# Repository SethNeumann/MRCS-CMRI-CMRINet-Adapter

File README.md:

# REPO NAME: MRCS-CMRI-CMRINet-Adapter

## License: Creative Commons Attribution-NonCommercial-ShareAlike

This is another wiring adapter for classic CMRI boards.  This one is for the CMRINet (RS485) line.  It plugs onto the 5 pin
male molex header (0.156) and brings out 2 sets of 0.100" (2.54mm) or 3.5mm pads for connection to the CMRINet.  This allows
connection without terminating a molex cable.  Note the spacing too tight for two on an SMINI so I've included two sets of screw 
terminals to support the daisy chain.

User Ed Klein requested this adapter.

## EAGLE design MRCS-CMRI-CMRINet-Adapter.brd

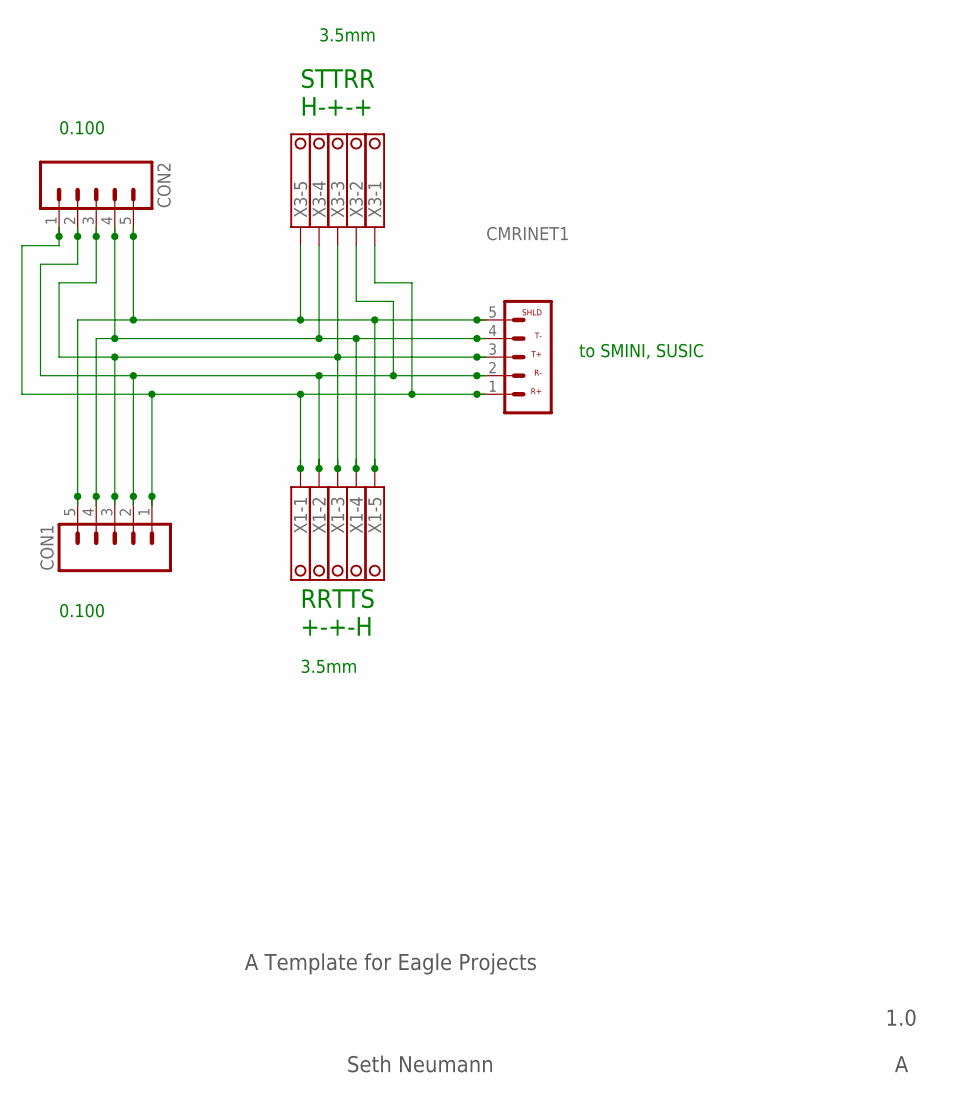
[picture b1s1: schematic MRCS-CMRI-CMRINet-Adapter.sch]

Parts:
CMRINET1: CONNECTOR-CMRINET.156; KK-156-5
CON1, CON2: CONNECTOR-M05LOCK; 1X05_LOCK
X1, X3: 1751277

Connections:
R+: CMRINET1.1, CON1.1, CON2.1, X1.1, X3.1
R-: CMRINET1.2, CON1.2, CON2.2, X1.2, X3.2
SHLD: CMRINET1.5, CON1.5, CON2.5, X1.5, X3.5
T+: CMRINET1.3, CON1.3, CON2.3, X1.3, X3.3
T-: CMRINET1.4, CON1.4, CON2.4, X1.4, X3.4

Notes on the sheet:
A Template for Eagle Projects
1.0
Seth Neumann
to SMINI, SUSIC
0.100
3.5mm
RRTTS +-+-H
STTRR H-+-+

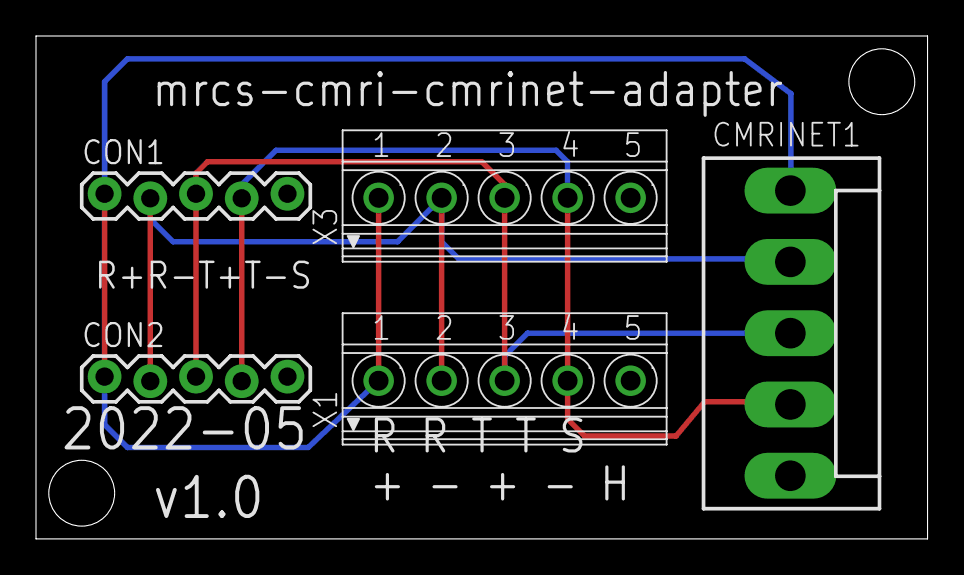
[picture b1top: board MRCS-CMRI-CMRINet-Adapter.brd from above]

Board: 2 copper layers, 49.5 x 27.9 mm, 7 parts (0 on the bottom side), 5 nets.

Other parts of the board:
U$1: CA-PROP65WARNING
U$2: MRCSLOGOBTM

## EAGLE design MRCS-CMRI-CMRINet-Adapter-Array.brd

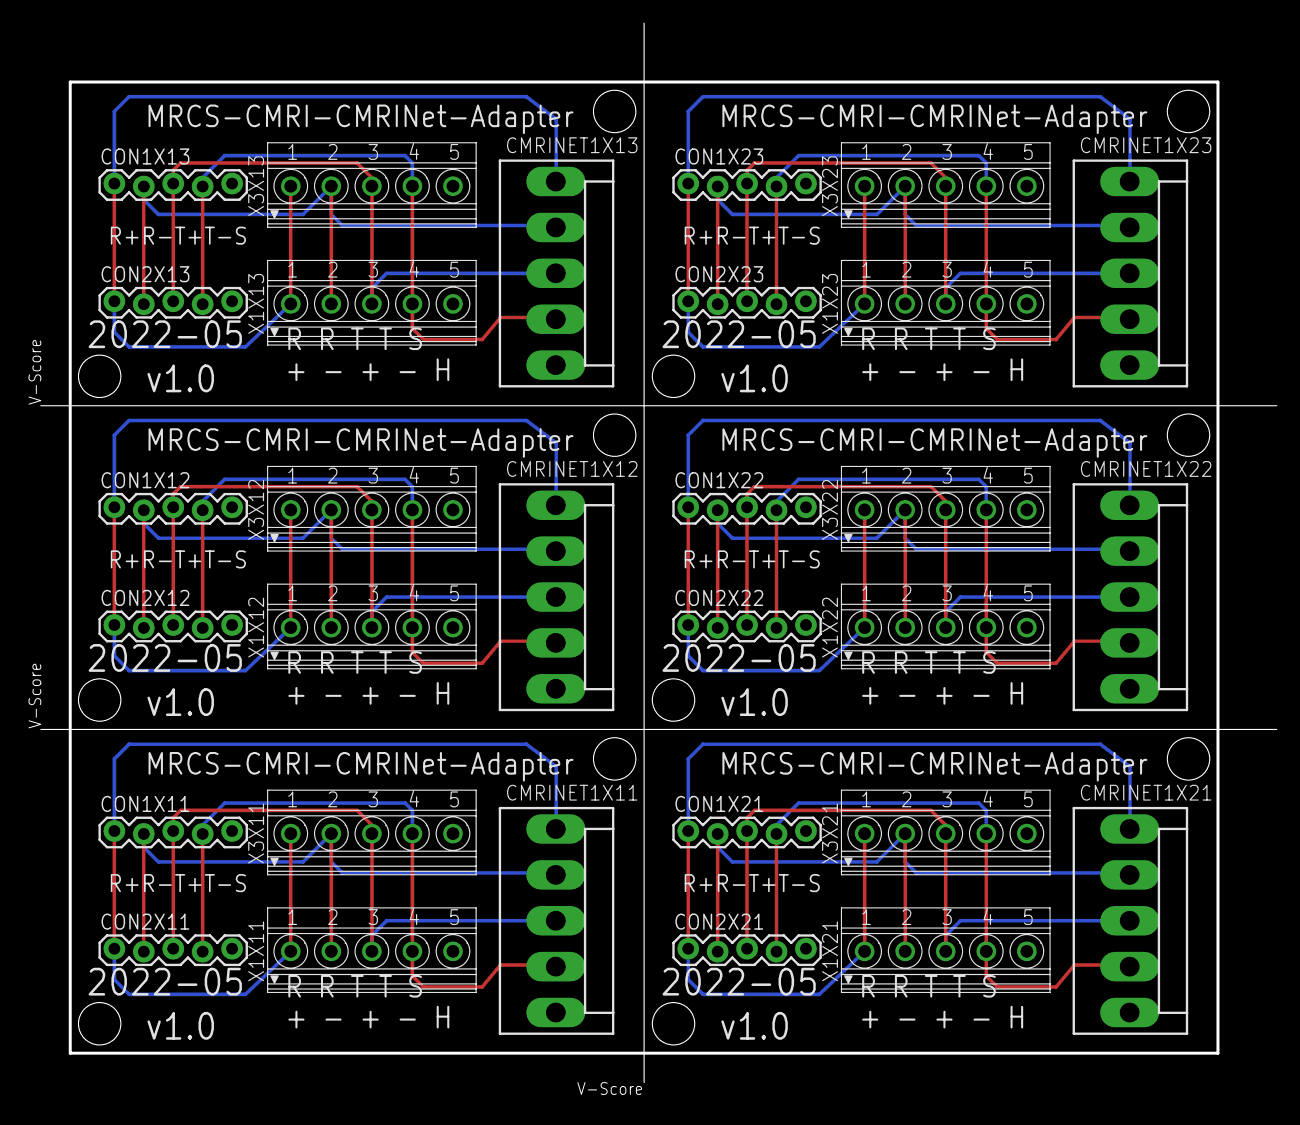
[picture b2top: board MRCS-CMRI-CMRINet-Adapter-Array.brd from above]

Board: 2 copper layers, 107.9 x 92.8 mm, 42 parts (0 on the bottom side), 30 nets.

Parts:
CMRINET1X11, CMRINET1X12, CMRINET1X13, CMRINET1X21, CMRINET1X22, CMRINET1X23: KK-156-5
CON1X11, CON1X12, CON1X13, CON1X21, CON1X22, CON1X23, CON2X11, CON2X12, CON2X13, CON2X21, CON2X22, CON2X23: 1X05_LOCK
U$1X11, U$1X12, U$1X13, U$1X21, U$1X22, U$1X23: CA-PROP65WARNING
U$2X11, U$2X12, U$2X13, U$2X21, U$2X22, U$2X23: MRCSLOGOBTM
X1X11, X1X12, X1X13, X1X21, X1X22, X1X23, X3X11, X3X12, X3X13, X3X21, X3X22, X3X23: 1751277

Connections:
R+X11: CMRINET1X11.1, CON1X11.1, CON2X11.1, X1X11.1, X3X11.1
R+X12: CMRINET1X12.1, CON1X12.1, CON2X12.1, X1X12.1, X3X12.1
R+X13: CMRINET1X13.1, CON1X13.1, CON2X13.1, X1X13.1, X3X13.1
R+X21: CMRINET1X21.1, CON1X21.1, CON2X21.1, X1X21.1, X3X21.1
R+X22: CMRINET1X22.1, CON1X22.1, CON2X22.1, X1X22.1, X3X22.1
R+X23: CMRINET1X23.1, CON1X23.1, CON2X23.1, X1X23.1, X3X23.1
R-X11: CMRINET1X11.2, CON1X11.2, CON2X11.2, X1X11.2, X3X11.2
R-X12: CMRINET1X12.2, CON1X12.2, CON2X12.2, X1X12.2, X3X12.2
R-X13: CMRINET1X13.2, CON1X13.2, CON2X13.2, X1X13.2, X3X13.2
R-X21: CMRINET1X21.2, CON1X21.2, CON2X21.2, X1X21.2, X3X21.2
R-X22: CMRINET1X22.2, CON1X22.2, CON2X22.2, X1X22.2, X3X22.2
R-X23: CMRINET1X23.2, CON1X23.2, CON2X23.2, X1X23.2, X3X23.2
SHLDX11: CMRINET1X11.5, CON1X11.5, CON2X11.5, X1X11.5, X3X11.5
SHLDX12: CMRINET1X12.5, CON1X12.5, CON2X12.5, X1X12.5, X3X12.5
SHLDX13: CMRINET1X13.5, CON1X13.5, CON2X13.5, X1X13.5, X3X13.5
SHLDX21: CMRINET1X21.5, CON1X21.5, CON2X21.5, X1X21.5, X3X21.5
SHLDX22: CMRINET1X22.5, CON1X22.5, CON2X22.5, X1X22.5, X3X22.5
SHLDX23: CMRINET1X23.5, CON1X23.5, CON2X23.5, X1X23.5, X3X23.5
T+X11: CMRINET1X11.3, CON1X11.3, CON2X11.3, X1X11.3, X3X11.3
T+X12: CMRINET1X12.3, CON1X12.3, CON2X12.3, X1X12.3, X3X12.3
T+X13: CMRINET1X13.3, CON1X13.3, CON2X13.3, X1X13.3, X3X13.3
T+X21: CMRINET1X21.3, CON1X21.3, CON2X21.3, X1X21.3, X3X21.3
T+X22: CMRINET1X22.3, CON1X22.3, CON2X22.3, X1X22.3, X3X22.3
T+X23: CMRINET1X23.3, CON1X23.3, CON2X23.3, X1X23.3, X3X23.3
T-X11: CMRINET1X11.4, CON1X11.4, CON2X11.4, X1X11.4, X3X11.4
T-X12: CMRINET1X12.4, CON1X12.4, CON2X12.4, X1X12.4, X3X12.4
T-X13: CMRINET1X13.4, CON1X13.4, CON2X13.4, X1X13.4, X3X13.4
T-X21: CMRINET1X21.4, CON1X21.4, CON2X21.4, X1X21.4, X3X21.4
T-X22: CMRINET1X22.4, CON1X22.4, CON2X22.4, X1X22.4, X3X22.4
T-X23: CMRINET1X23.4, CON1X23.4, CON2X23.4, X1X23.4, X3X23.4

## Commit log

2022-05-08 final tweaks on first pass of adapter
    Changed the 5 position 3.5mm as the labels didn't agree with the positions on the SMINI board. I may need to revisit this after testing.
2022-07-05 changes to support panelization
    panelized (2x3) and removed miscellaneous gerbs and work files
